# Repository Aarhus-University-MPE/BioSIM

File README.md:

# BioSIM - Bioaerosol Simulation Chamber

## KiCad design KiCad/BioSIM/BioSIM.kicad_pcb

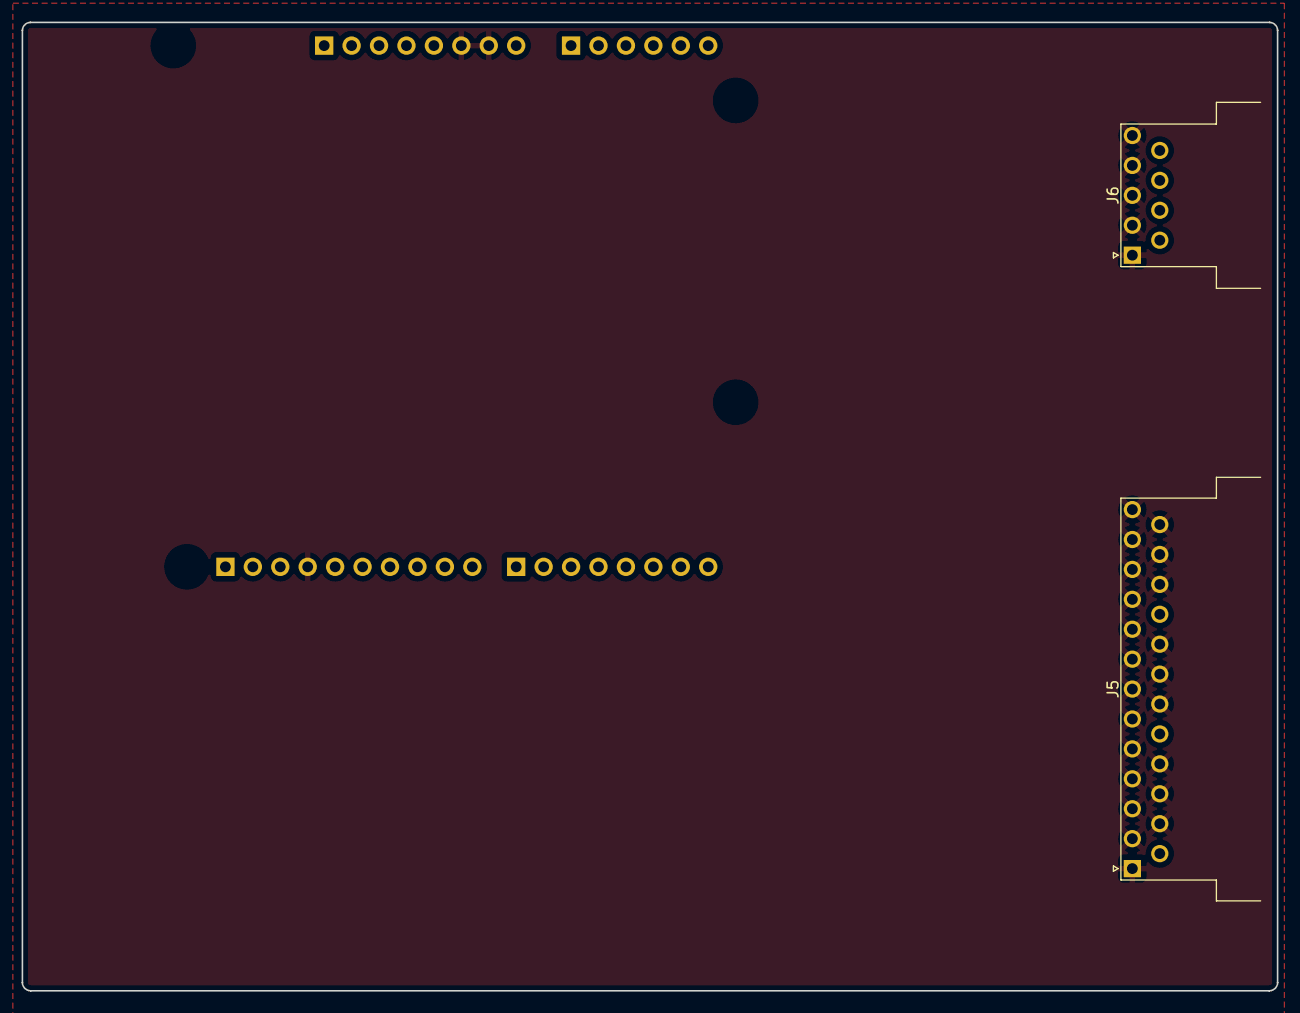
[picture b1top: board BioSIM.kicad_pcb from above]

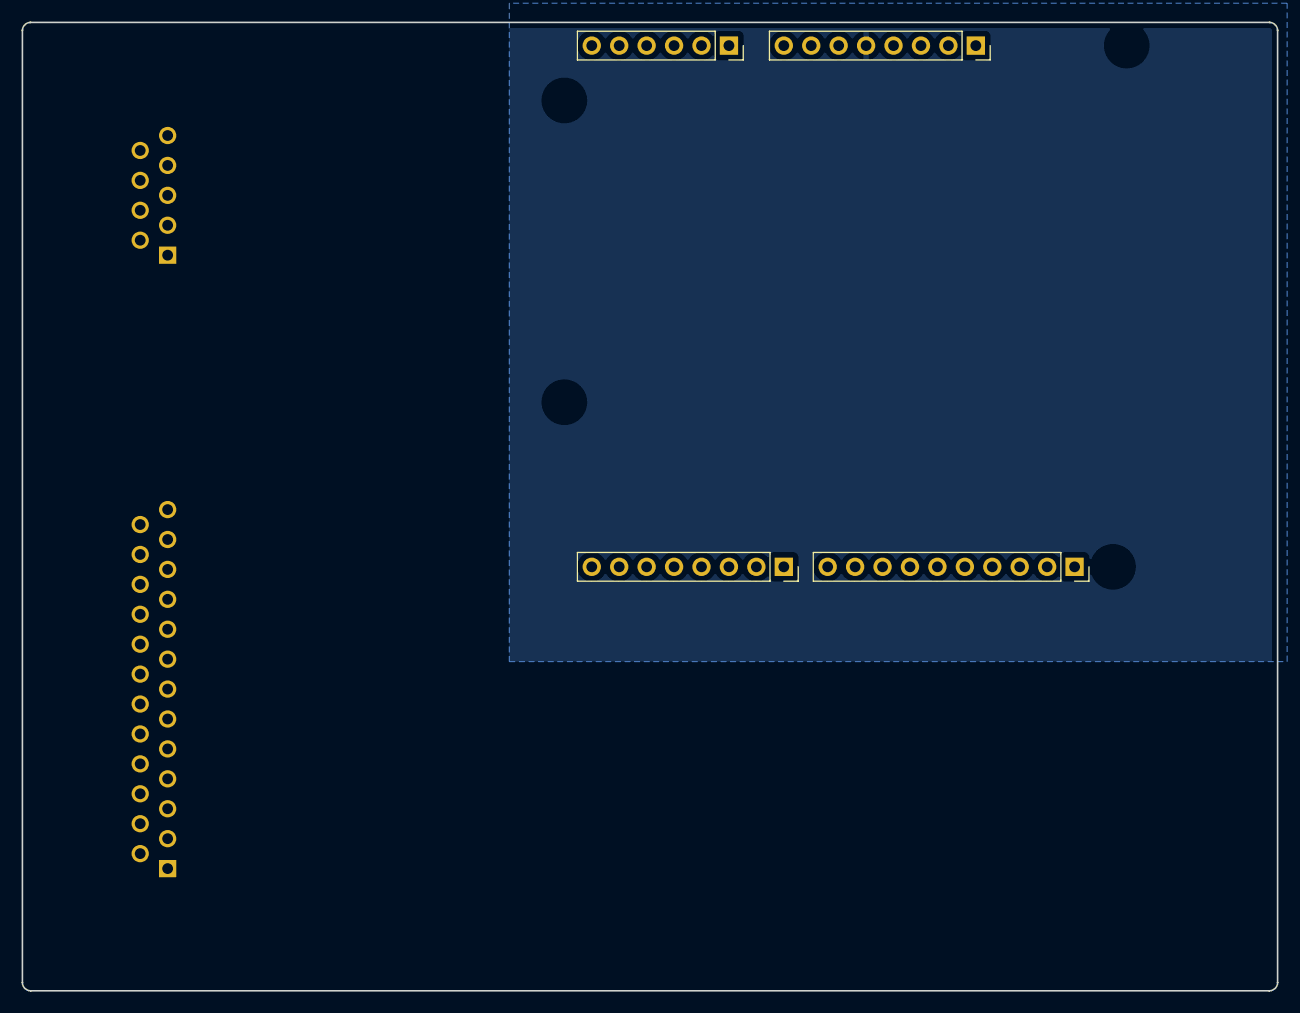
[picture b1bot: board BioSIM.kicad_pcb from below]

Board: 2 copper layers, 116.2 x 89.7 mm, 6 parts (4 on the bottom side), 5 nets, no tracks yet.

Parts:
J1: Power; PinSocket_1x08_P2.54mm_Vertical
J2: Digital/PWM; PinSocket_1x10_P2.54mm_Vertical
J3: Analog; PinSocket_1x06_P2.54mm_Vertical
J4: Digital/PWM; PinSocket_1x08_P2.54mm_Vertical
J5: DB25_Male; DSUB-25_Male_Horizontal_P2.77x2.54mm_EdgePinOffset9.40mm
J6: DB9_Male; DSUB-9_Male_Horizontal_P2.77x2.54mm_EdgePinOffset9.40mm

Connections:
/SCL/A5: J2.1, J3.6
/SDA/A4: J2.2, J3.5
AC Adjust: J5.22, J6.7
Freq Adjust: J5.14, J6.6
GND: J1.6, J1.7, J2.4, J5.1, J5.2, J5.3, J5.4, J5.5, J5.6, J5.7, J5.8, J5.9, J5.10, J5.11, J5.12, J5.13, J5.15, J5.16, J5.17, J5.19, J5.20, J5.21, J5.23, J5.24, J5.25, J6.1, J6.2, J6.3, J6.4, J6.5

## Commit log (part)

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2022-11-03 File Setup
2022-11-03 LabVIEW init
2022-11-03 manuals
2022-12-14 DataLogger
2022-12-15 TLogger NI Init Bug Fix
2022-12-17 BioSIM Controller Boilerplate
2022-12-29 KiCad Setup
2023-09-19 Preliminary Setup
    Splash Screen, Color Scheme
2023-10-20 cDAQ connection
2023-10-23 UI Setup
2023-10-24 Cluster converter
2023-11-01 UX setup
2023-11-01 Stack rebuild
2023-11-06 Build Configurations Updated
2023-11-06 System restructure
    Moved Clusters, and Buffer setup
    Minor helper functions
2023-11-12 Project Rebuild
2023-11-24 System Control Setup
2024-01-09 Full Software Documentation and Comments
2024-01-16 Data Save Structure
2024-01-17 Computer Vision Algorithm
2024-01-18 Computer Vision and PID control
2024-01-19 System Test
2024-01-22 Rebuild after crash
2024-01-22 Rebuild
2024-01-22 SystemTest
2025-10-24 Okey der er meget
2025-10-28 It seems to be working as intended
    Humidity hass been added
2025-11-05 Changes to save all data from Humidity sensor.
    Made changes to save and display all data collected from Chilled Mirror Hydrometer.
2025-11-05 New release
2026-02-18 a few small isues
2026-06-22 Changes to save data and file reads
    Some of it works now, some things don't.
2026-06-23 Should be okey
2026-06-25 Fixed errors related to saving data and files
